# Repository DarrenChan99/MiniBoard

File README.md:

# MiniBoard
A 3x3 macro pad with OLED display. 
One idea to use this layout is to keep track of daily habits and track them to promote better productivity.

<h2> Key Mapping </h2>

<ul>
<li>[1-6]: Up to 6 individual habits that can be mapped</li>
<li>[7 + 8]: Used to navigate across the individual habits and the consistancy overtime </li>
<li>[9]: Reset the board</li>
</ul>

<h2>Why?</h2>
<ol>
 <li>I wanted to learn electronics and pcb design</li>
 <li>Create a real world design that is functional</li>
 <li>Explore new enviroments like KiCad and Fusion 360</li>
</ol>

<h1> CAD </h1>

<h1> PCB </h1>
<p>Made with KiCad</p>

<p> Schematic </p>

<p> PCB </p>

<h1> Firmware </h1>
<p> This macropad used <a href="https://github.com/KMKfw/kmk_firmware">KMK</a> firmware with CircuitPython. </p>
<ul> 
 <li>Used to implment button mapping</li>
 <li>Displaying and refreashing OLED</li>
</ul>
<h1> BOM </h1>
<table>
    <thead>
        <tr>
            <th>Component</th>
            <th>Quantity</th>
            <th>Description</th>
        </tr>
    </thead>
    <tbody>
        <tr>
            <td>Seeed Studio XIAO RP2040</td>
            <td>1</td>
            <td>Microcontroller board</td>
        </tr>
        <tr>
            <td>Cherry MX Switches</td>
            <td>9</td>
            <td>Mechanical key switches</td>
        </tr>
        <tr>
            <td>DSA Keycaps</td>
            <td>9</td>
            <td>Blank Keycaps</td>
        </tr>
        <tr>
            <td>0.91" OLED Display</td>
            <td>1</td>
            <td>4 pin I2C display</td>
        </tr>
        <tr>
            <td>1N4148 Diodes</td>
            <td>6</td>
            <td>Through-hole signal diodes</td>
        </tr>
        <tr>
            <td>M3x5x4 Heatset Inserts</td>
            <td>4</td>
            <td>Threaded inserts for case assembly</td>
        </tr>
        <tr>
            <td>M3x16mm Screws</td>
            <td>4</td>
            <td>Mounting case</td>
        </tr>
        <tr>
            <td>3D Printed Case</td>
            <td>1</td>
            <td>2-part custom enclosure</td>
        </tr>
        <tr>
            <td>Soldering Iron</td>
            <td>1</td>
            <td>Assembly tool</td>
        </tr>
    </tbody>
</table>

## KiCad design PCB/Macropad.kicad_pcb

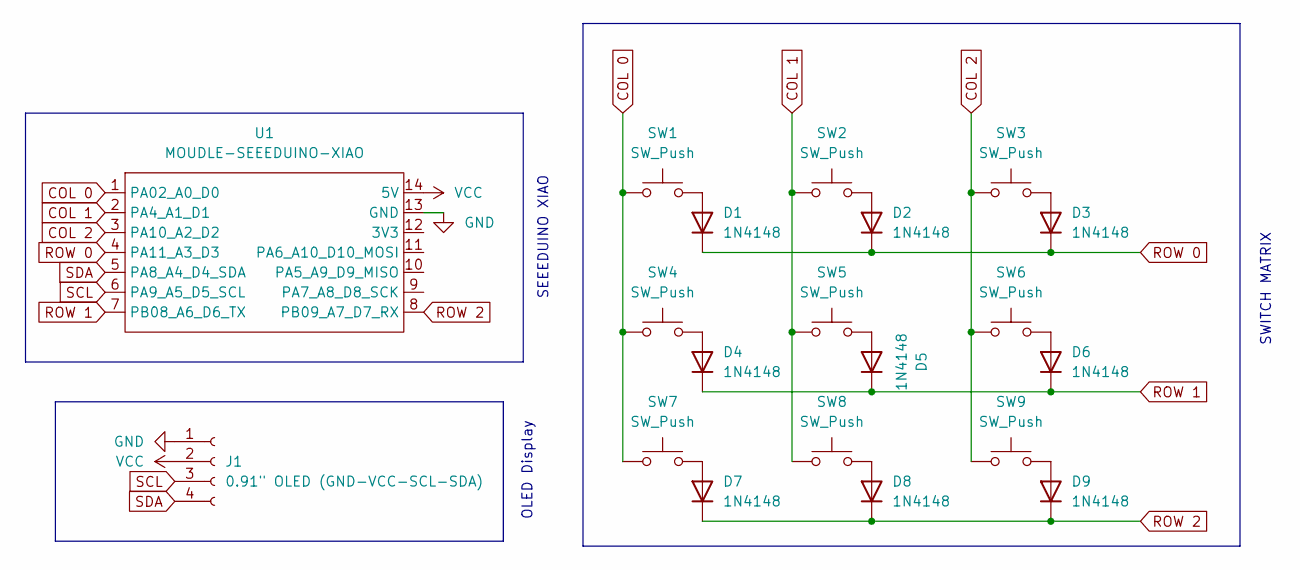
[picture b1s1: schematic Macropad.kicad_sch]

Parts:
D1, D2, D3, D4, D5, D6, D7, D8, D9: 1N4148; D_DO-35_SOD27_P7.62mm_Horizontal
J1: 0.91" OLED (GND-VCC-SCL-SDA); SSD1306-0.91-OLED-4pin-128x32
SW1, SW2, SW3, SW4, SW5, SW6, SW7, SW8, SW9: SW_Push; SW_Cherry_MX_1.00u_PCB
U1: MOUDLE-SEEEDUINO-XIAO; XIAO-Generic-Hybrid-14P-2.54-21X17.8MM

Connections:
COL 0: SW1.1, SW4.1, SW7.1, U1.1 (PA02_A0_D0)
COL 1: SW2.1, SW5.1, SW8.1, U1.2 (PA4_A1_D1)
COL 2: SW3.1, SW6.1, SW9.1, U1.3 (PA10_A2_D2)
GND: J1.1, U1.13 (GND)
unnamed: D1.2 (A), SW1.2
unnamed: D2.2 (A), SW2.2
unnamed: D3.2 (A), SW3.2
unnamed: D4.2 (A), SW4.2
unnamed: D5.2 (A), SW5.2
unnamed: D6.2 (A), SW6.2
unnamed: D7.2 (A), SW7.2
unnamed: D8.2 (A), SW8.2
unnamed: D9.2 (A), SW9.2
ROW 0: D1.1 (K), D2.1 (K), D3.1 (K), U1.4 (PA11_A3_D3)
ROW 1: D4.1 (K), D5.1 (K), D6.1 (K), U1.7 (PB08_A6_D6_TX)
ROW 2: D7.1 (K), D8.1 (K), D9.1 (K), U1.8 (PB09_A7_D7_RX)
SCL: J1.3, U1.6 (PA9_A5_D5_SCL)
SDA: J1.4, U1.5 (PA8_A4_D4_SDA)
VCC: J1.2, U1.14 (5V)

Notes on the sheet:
OLED Display
SEEEDUINO XIAO
SWITCH MATRIX

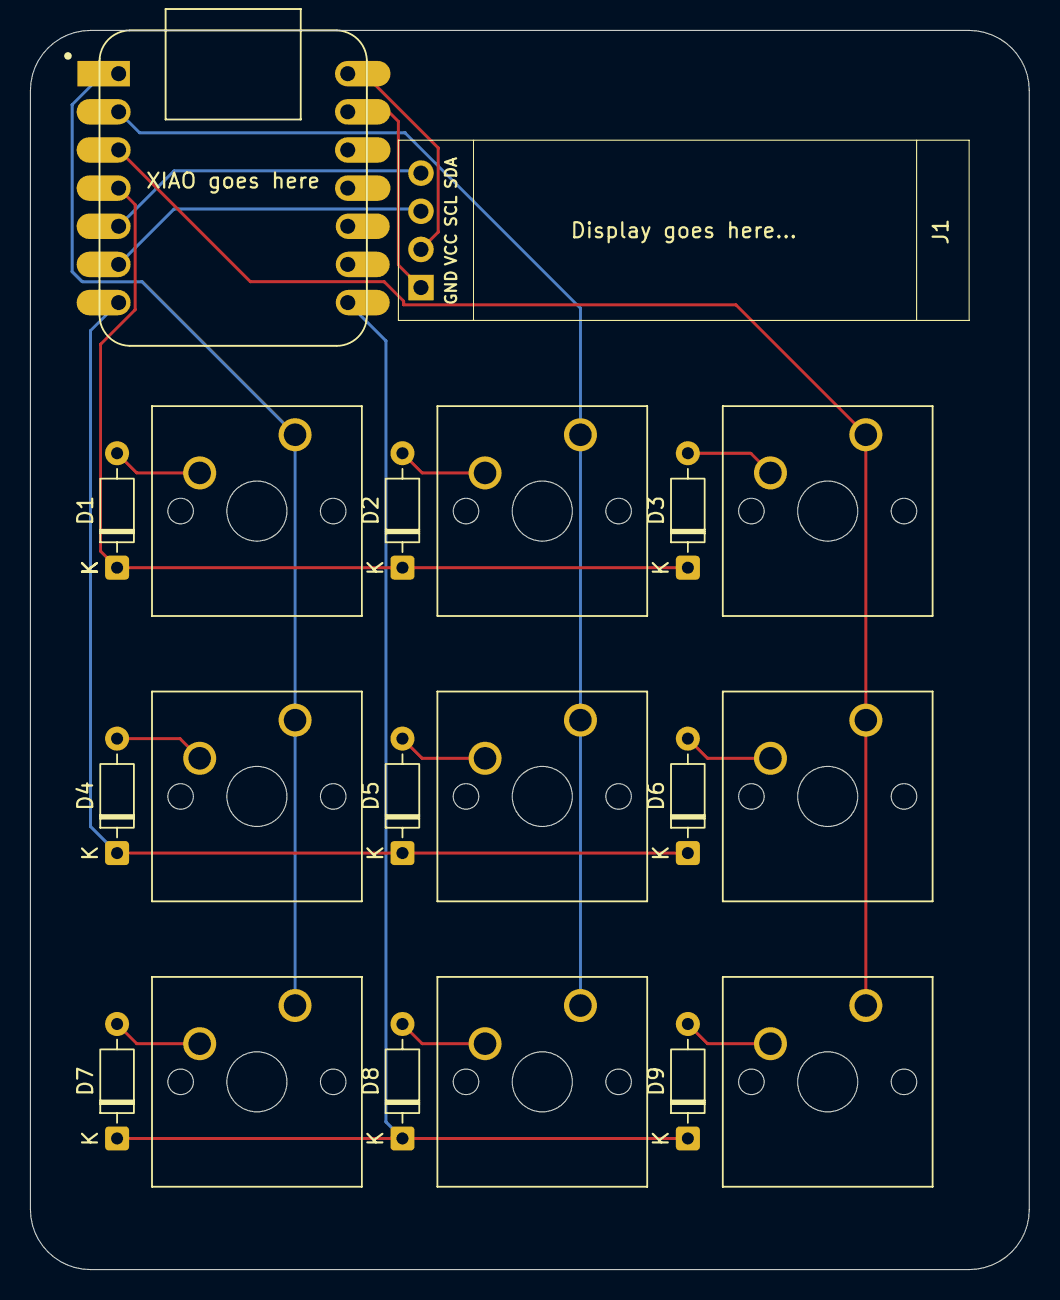
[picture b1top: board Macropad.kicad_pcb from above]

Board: 2 copper layers, 66.5 x 82.5 mm, 20 parts (0 on the bottom side), 19 nets.

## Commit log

2026-03-21 read me
2026-03-21 Update README with CAD, PCB, Firmware, and BOM details
    Added sections for CAD, PCB, Firmware, and BOM with relevant images and descriptions.
2026-03-21 Refactor README.md with HTML formatting
    Updated formatting and structure of the README to use HTML tags for better presentation.
2026-03-21 updated BOM
2026-03-21 added cad file
2026-03-21 files and folders
2026-03-21 actually added the files
2026-03-22 added some starter code
2026-03-22 added file and folder
2026-03-22 finished most code
2026-03-22 production file
2026-03-22 productiion folder
2026-03-22 firmware folder
2026-03-22 added required pro and individual files
2026-03-22 code change
2026-03-22 fixed image
2026-03-22 added f3d file
2026-03-22 added step files
2026-03-23 new cad files
2026-03-27 Replace CAD image with a new screenshot
    Updated image in CAD section of README.
